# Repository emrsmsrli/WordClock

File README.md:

# WORD CLOCK ARDUINO

The code in this repository is a heavily modified version of 
[Tinker's Word Clock code](http://www.instructables.com/id/Tinkers-Word-Clock-REVISITED-NOW-110-More-AWESOME-/). 
And uses a modified version of [OneButton](https://github.com/mathertel/OneButton) library.

## TODO
- [x] Add second support alongside of minutes and hours
- [x] Make the leds fade-in and -out when a change in time or color happens
- [x] Use external interrupts to count button clicks so we can increment both hour and minute with a single button
- [x] Implement smoothstep interpolation to led animations
- [x] Implement night mode, where overall led intensity is 0.125 instead of 1.0
- [x] Implement happy birthday mode
- [x] Add documentation

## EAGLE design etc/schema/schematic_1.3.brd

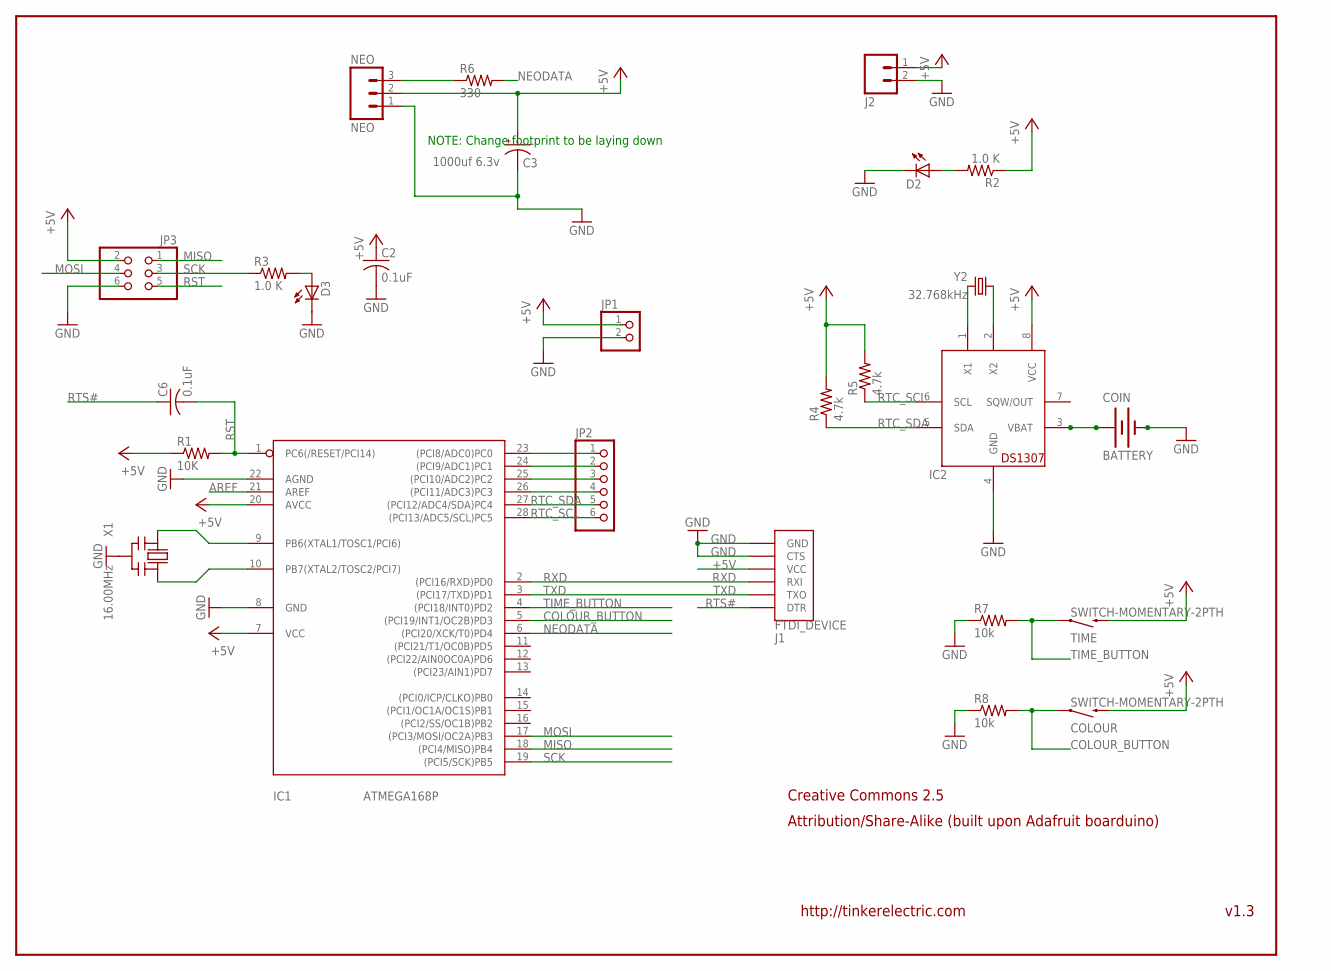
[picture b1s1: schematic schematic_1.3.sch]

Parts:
C2, C6: 0.1uF; C025-025X050
C3: 1000uf 6.3v; E5-10,5
COIN: BATTERY; BATTCOM_12MM
COLOUR: SWITCH-MOMENTARY-2PTH; TACTILE-PTH
D2: LED3MM
D3: Green; LED3MM
IC1: ATMEGA168P; DIL28/3
IC2: DS1307; DIL08
J1: FTDI_DEVICE; FTDI_DEVICE_SIDE
J2: M02POLAR; MOLEX-1X2
JP1: PINHD-1X2CB; 1X02-CB
JP2: PINHD-1X6CB; 1X06-CLEANBIG
JP3: PINHD-2X3; 2X03
NEO: NEO; MOLEX-1X3
R1: 10K; 0204V
R2, R3: 1.0 K; 0204V
R4, R5: 4.7k; 0204V
R6: 330; 0204V
R7, R8: 10k; 0204V
TIME: SWITCH-MOMENTARY-2PTH; TACTILE-PTH
X1: 16.00MHz; CERM_OSC
Y2: 32.768kHz; TC26HEZ

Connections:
+5V: C2.1, C3.+, COLOUR.3 (2), IC1.7 (VCC), IC1.20 (AVCC), IC2.8 (VCC), J1.P$4 (VCC), J2.1, JP1.1, JP3.2, NEO.2, R1.1, R2.1, R4.2, R5.2, TIME.3 (2)
AREF: IC1.21 (AREF)
COLOUR_BUTTON: COLOUR.1, IC1.5 ((PCI19/INT1/OC2B)PD3), R8.2
GND: C2.2, C3.-, COIN.-, D2.K (C), D3.K (C), IC1.8 (GND), IC1.22 (AGND), IC2.4 (GND), J1.P$5 (CTS), J1.P$6 (GND), J2.2, JP1.2, JP3.6, NEO.1, R7.1, R8.1, X1.P$2 (GND)
MISO: IC1.18 ((PCI4/MISO)PB4), JP3.1
MOSI: IC1.17 ((PCI3/MOSI/OC2A)PB3), JP3.4
unnamed: IC1.9 (PB6(XTAL1/TOSC1/PCI6)), X1.P$1 (IN)
unnamed: IC1.10 (PB7(XTAL2/TOSC2/PCI7)), X1.P$3 (OUT)
unnamed: D2.A, R2.2
unnamed: D3.A, R3.2
unnamed: NEO.3, R6.1
unnamed: IC2.2 (X2), Y2.1
unnamed: IC2.1 (X1), Y2.2
unnamed: COIN.+, IC2.3 (VBAT)
unnamed: IC1.23 ((PCI8/ADC0)PC0), JP2.1
unnamed: IC1.24 ((PCI9/ADC1)PC1), JP2.2
unnamed: IC1.25 ((PCI10/ADC2)PC2), JP2.3
unnamed: IC1.26 ((PCI11/ADC3)PC3), JP2.4
NEODATA: IC1.6 ((PCI20/XCK/T0)PD4), R6.2
RST: C6.2, IC1.1 (PC6(/RESET/PCI14)), JP3.5, R1.2
RTC_SCL: IC1.28 ((PCI13/ADC5/SCL)PC5), IC2.6 (SCL), JP2.6, R5.1
RTC_SDA: IC1.27 ((PCI12/ADC4/SDA)PC4), IC2.5 (SDA), JP2.5, R4.1
RTS#: C6.1, J1.P$1 (DTR)
RXD: IC1.2 ((PCI16/RXD)PD0), J1.P$3 (RXI)
SCK: IC1.19 ((PCI5/SCK)PB5), JP3.3, R3.1
TIME_BUTTON: IC1.4 ((PCI18/INT0)PD2), R7.2, TIME.1
TXD: IC1.3 ((PCI17/TXD)PD1), J1.P$2 (TXO)

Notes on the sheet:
v1.3
http://tinkerelectric.com
Creative Commons 2.5
Attribution/Share-Alike (built upon Adafruit boarduino)
NOTE: Change footprint to be laying down

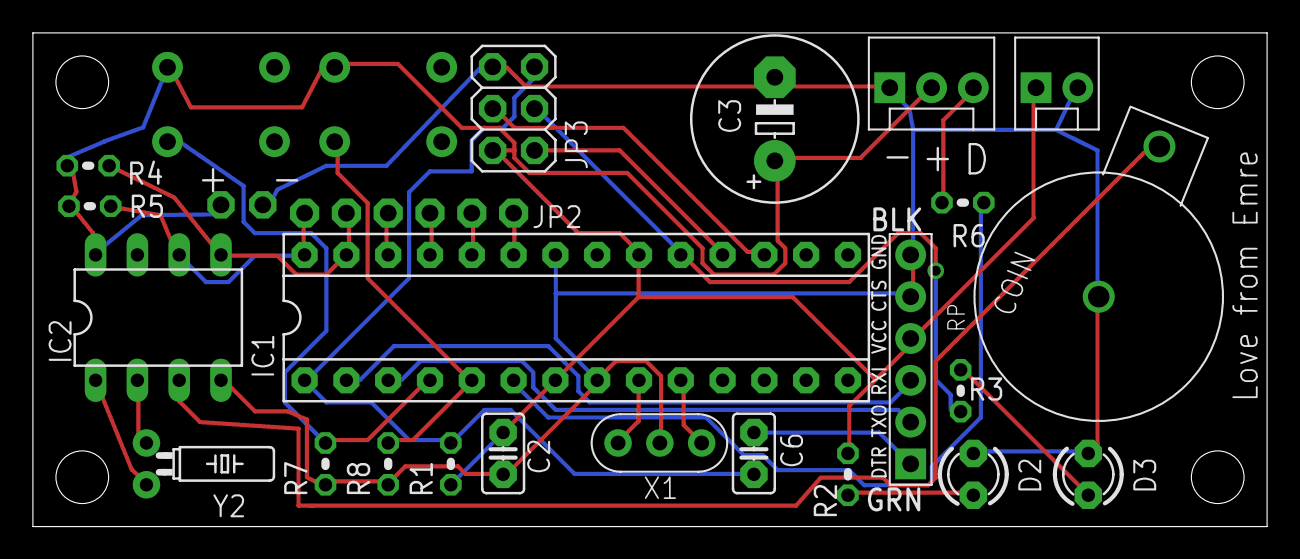
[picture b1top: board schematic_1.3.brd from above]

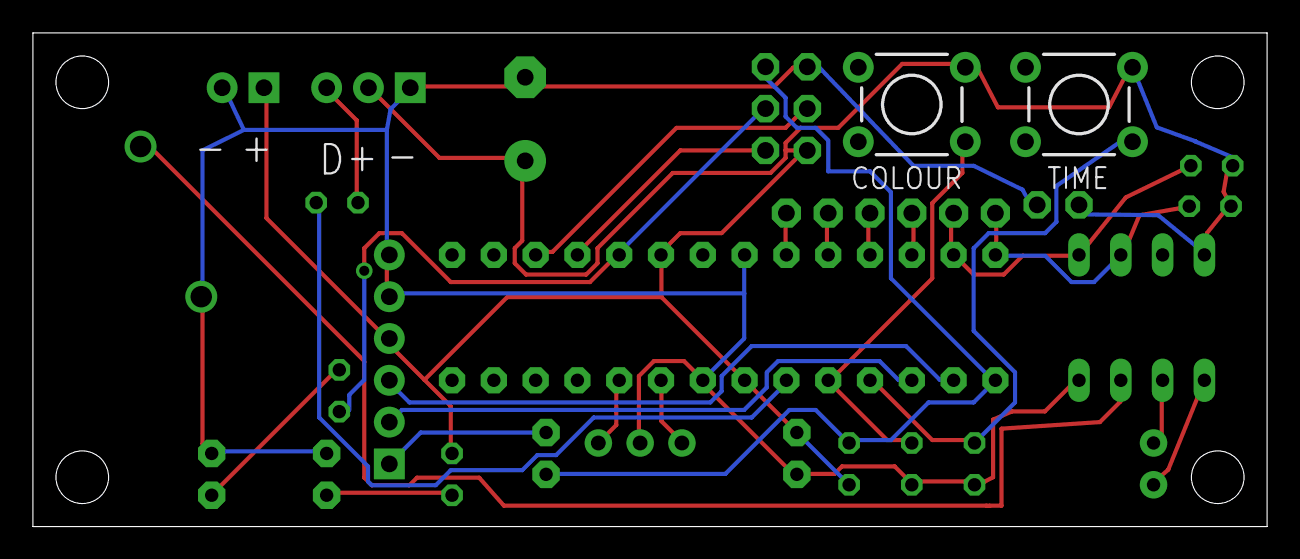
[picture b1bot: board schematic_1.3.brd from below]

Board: 2 copper layers, 75.0 x 30.0 mm, 26 parts (2 on the bottom side), 26 nets.

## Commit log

2018-01-31 ignore
2018-01-31 init
2018-01-31 cmakelists
2018-01-31 refactor led enabling disabling
2018-01-31 move all leds by 1
2018-02-01 remove global equals and add member operator!=
2018-02-01 fix 20->25 and 25->20 minute transitions
2018-02-01 fix operator!=
2018-02-01 - make sure the pixels fade-in when program starts. - change delay() functions with counters in time button and color button - pixels now fade in and out when color button is pressed
2018-02-02 make allowed delays united, so time change can occur automatically in loop(). also fix button timers not updating
2018-02-02 fade_in() and fade_out now in set_brightness() for better maintainability
2018-02-02 remove unnecessary tick() call from on_time_button_pressed()
2018-02-02 separate allowed times for color and time buttons, again
2018-02-03 remove time constraints on buttons because external interrupts are not available by default
2018-02-05 - function and #define location changes - refactor calculation of minutes - skip current iteration of loop() if no led has been changed since the last iteration - fix when O_OCLOCK is on, M_5 would a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
2018-02-05 implement night mode to work between h22-h8
2018-02-05 Revert "implement night mode to work between h22-h8"
    This reverts commit 2964def
2018-02-06 - use OneButton lib - change struct time_s with class Time - rename class led to class LedArray
2018-02-06 replace OneButton lib with custom impl
2018-02-06 fix compilation errors
2018-02-06 rename some enum values in Button
2018-02-06 include a todo readme file
2018-02-06 remove backup copies from git
2018-02-06 add LICENSE file
2018-02-06 implement smoothstep interpolation
2018-02-07 define MAX_BRIGHTNESS
2018-02-07 fix perform_clicks() won't check for click events if button state machine in PRESSED or RELEASED
2018-02-07 fix set_pixel_brightness calculates smooth_step with 255 instead of MAX_BRIGHTNESS
2018-02-07 - do some refactoring - animation time is now 250ms
2018-02-07 add a todo item
2018-02-07 zero = 0x0 probably wouldn't disable and enable oscillator, make it zero = (byte)0x00
2018-02-07 - more refactor - remove unnecessary call to Wire.write()
2018-02-07 Revert "add a todo item"
    This reverts commit 8756d52
2018-02-07 Revert "Revert "add a todo item""
    This reverts commit fc62dd9
2018-02-08 - keep track of date as well as time - fix some time read masks - move hour overflow check in on_t_b_pressed() inside of min overflow check
2018-02-08 implement birthday mode and hope no bugs are present
2018-02-08 cross-over a birthday mode todo
2018-02-08 birthday mode now initiates at 9 am and 6 pm
2018-02-09 fix time change animation after celebration is over
2018-02-10 remove Birthday::begin()
2018-02-10 check if celebration is already cancelled when time button is pressed
2018-02-10 implement happy birthday song!
2018-02-10 Revert "remove Birthday::begin()"
    This reverts commit 6e99953
2018-02-10 - move #define statements to another file - refactor to musical
2018-02-10 fix minute_led is initialized to M_5 instead of M_NONE
2018-02-10 consts.h
2018-02-10 remove unnecessary casts to uint_8 in bright() and dim()
2018-02-10 set delay in set_brightness() to 1000 from 500, animation time is 250ms for single fade-ins or -outs
2018-02-10 seconds will stay as it is.
2018-02-12 make animation for loops a #define clause for simplicity
2018-02-12 remove time struct name for it wont ever be used again
2018-02-12 seconds_led now ranges from 1-5 instead of 0-4
2018-02-12 refactor color shifting so we can shift one color to another easily when color button is pressed
2018-02-12 implement current_color() instead of array access
2018-02-12 ANIMATE() macro now accepts a variable name for brevity
2018-02-12 change the signature of shift_color() and refactor names of shift_color_all() parameters
2018-02-12 fix seconds_led is incorrectly initialized to zero instead of one since we changed the algorithm to compute the led index
2018-02-12 - fix typo in name of dec2bcd - fix bcd2dec does not cast the whole computation
2018-02-13 - change the signature of shift_color_heart() - implement double-click color button manually triggers birthday mode
2018-02-13 remove unnecessary call to pixels.clear()
2018-02-13 color button now also disables birthday mode
2018-02-19 add pixels.show() to init the strip as all black
2018-03-01 implement long pressing to button lib
2018-03-01 Revert "implement long pressing to button lib"
    This reverts commit 53eb45d
2018-03-01 add digital clock implementation todo
2018-03-09 change speaker pin to pin7
2018-03-09 remove claret as it is impossible to light with leds
2018-03-09 add a set method to color_t
2018-03-09 implement night mode, finally!
2018-03-15 move one time used heart: int[] inside the shift_color_heart() function
2018-03-15 move manual_begin to the beginning of the check, so is_today() won't check for time if manual_begin triggered
2018-03-16 fix after a brightness change, leds won't shift to their new states gracefully
2018-03-16 add function prototypes to consts.h and rename it to wordclock.h
2018-03-16 fix smooth_step shifts from new to old instead of vice versa
2018-03-20 fix interrupts() are not called if no button is pressed
2018-03-20 fix very upper part of the heart not lit
2018-03-20 fix time and color button pins are needs to change
2018-03-20 change the way color changes because of brightness adjustments
2018-03-20 use RTClib instead of custom rtc implementation
2018-03-20 use 900 us delay when shifting colors instead of 1000
2018-03-21 make led array range upper bound exclusive (this fixes led0 being lit)
2018-03-21 - code style changes - wait for 950ms instead of 1000ms while waiting for birthday mode to finish - use tick() to avoid code duplication
2018-03-21 fix brightness assignment is incorrect
2018-03-22 change the pin numbers of the buttons because i'm an idiot and burnt the color button while soldering
2018-03-23 - add an is_night() method to query the time of the day. - add a night check to setup() so if clock is plugged in at night it will start with a low brightness
2018-03-25 add a todo item: add documentation
2018-04-05 make animation time 100ms as it is a necessary thing to do in order to prevent second skipping
2018-04-05 fix initial brightness is calculated incorrectly
2018-04-05 make night time start at 10pm instead of 11pm
2018-04-05 fix indentation of the array initializers
2018-04-05 documentation
2018-04-05 change ambiguous variable name b to shifted
2018-04-05 change the way casts are happened. add some more casts for safety.
2018-04-05 - rename wordclock.h to wordclock.hpp - missing cast in wordclock.hpp
2018-05-31 - separate Button and LedArray classes to their own files - move docs to header files - reformat code
2018-05-31 - move more defines to relevant headers - move music related stuff to music.hpp and music.cpp
2018-05-31 introduce delay_short() and use wherever possible
2018-06-13 keep track of drag minutes and increment the time by one min every month
2018-06-13 update include statements
2018-06-13 update cmake
2018-10-01 add additional resources to build the clock
2018-10-08 fix 'accuracy fix' does not actually fixed the problem
2018-11-18 rearrange hours since clock gives the wrong hour shown
2018-11-18 remove accuracy calculation and add first time run code
2018-11-18 fix birthday

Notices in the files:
parts and their libraries:
SparkFun-FreqCtrl: Licensing: Creative Commons ShareAlike 4.0 International - https://creativecommons.org/licenses/by-sa/4.0
